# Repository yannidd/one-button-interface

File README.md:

# One Button Interface

PCB layout and schematic and Arduino code for a single push-button interface that can be used to turn a device on/off as well as a user input to interact with the firmware on a microcontroller.

## BOM

Reference   | Quantity| Value                                                                       | RS Stock No.| Vendor
|-          |-        |-                                                                            |-            |-
C1 C2 C3 C5 |4        |1uF                                                                          |461-2708     |RS
C4          |1        |0.1uF                                                                        |264-4630     |RS
H1 H2 H3 H4 |4        |MountingHole                                                                 |~
J1          |1        |[Conn_01x02](https://docs.rs-online.com/cb9d/0900766b81347511.pdf)           |820-1494     |RS
J6          |1        |[Conn_01x04](https://docs.rs-online.com/cd6a/0900766b813c4c2e.pdf)           |360-6314     |RS
R1          |1        |10K                                                                          |182-9211     |RS
SW1         |1        |[PTS645SL50SMTR 92 LFS](https://docs.rs-online.com/62d0/0900766b815a8e9b.pdf)|135-9400     |RS
U1          |1        |[LD39015M33R](http://www.st.com/resource/en/datasheet/ld39015.pdf)           |795-8965     |RS
U2          |1        |[STM6600](http://www.st.com/resource/en/datasheet/stm6600.pdf)               |189-2069     |RS

## Directory Tree

- arduino - Arduino source code with an example application.
- img - Supplementary images
- pcb - PCB schematic, layout and BOM.
  - kicad - Design files for KiCad EDA.

## Connection Diagram

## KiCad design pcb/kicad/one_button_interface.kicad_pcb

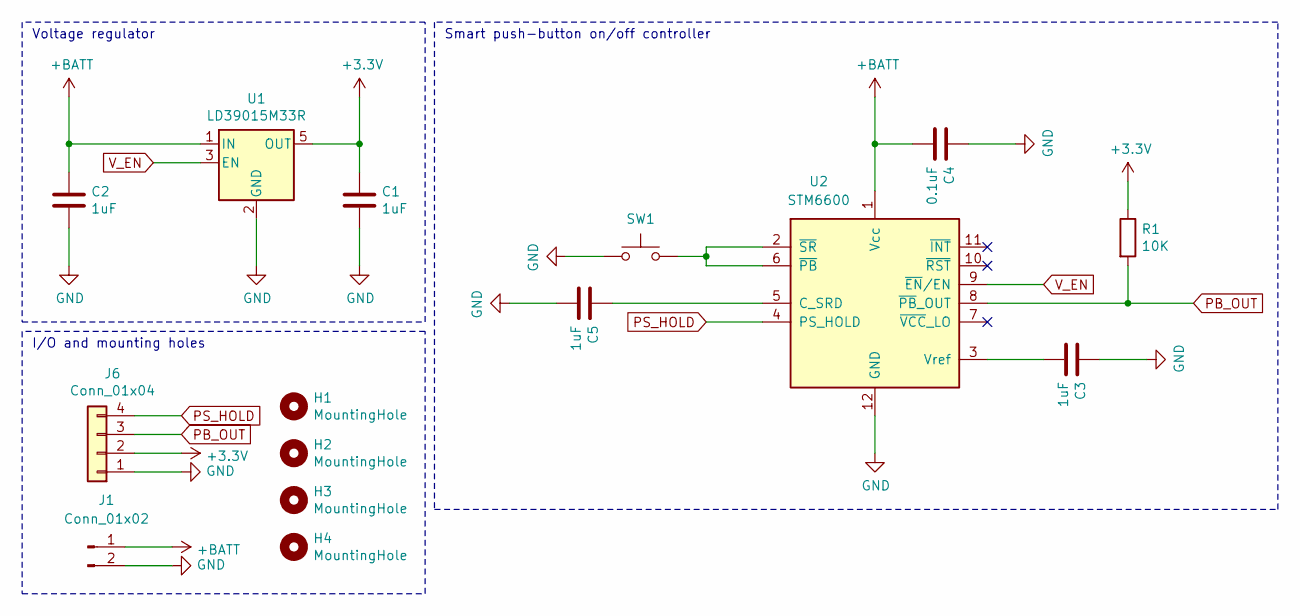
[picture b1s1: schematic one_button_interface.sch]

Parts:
C1, C2, C3, C5: 1uF; C_0603_1608Metric_Pad1.08x0.95mm_HandSolder
C4: 0.1uF; C_0603_1608Metric_Pad1.08x0.95mm_HandSolder
H1, H2, H3, H4: MountingHole; MountingHole_M1.6
J1: Conn_01x02; JST_PH_S2B-PH-K_1x02_P2.00mm_Horizontal
J6: Conn_01x04; PinHeader_1x04_P2.54mm_Vertical
R1: 10K; R_0603_1608Metric_Pad0.98x0.95mm_HandSolder
SW1: PTS645SL50SMTR 92 LFS; SW_SPST_PTS645
U1: LD39015M33R; SOT-23-5
U2: STM6600; TDFN-12_2x3mm_P0.5mm

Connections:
+3V3: C1.1, J6.2, R1.1, U1.5 (OUT)
+BATT: C2.1, C4.2, J1.1, U1.1 (IN), U2.1 (Vcc)
GND: C1.2, C2.2, C3.1, C4.1, C5.2, J1.2, J6.1, SW1.1, U1.2 (GND), U2.12 (GND)
unnamed: C3.2, U2.3 (Vref)
unnamed: C5.1, U2.5 (C_SRD)
unnamed: SW1.2, U2.2 (~SR~), U2.6 (~PB~)
PB_OUT: J6.3, R1.2, U2.8 (~PB~_OUT)
PS_HOLD: J6.4, U2.4 (PS_HOLD)
V_EN: U1.3 (EN), U2.9 (~EN~/EN)

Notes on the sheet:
Voltage regulator
Smart push-button on/off controller
I/O and mounting holes

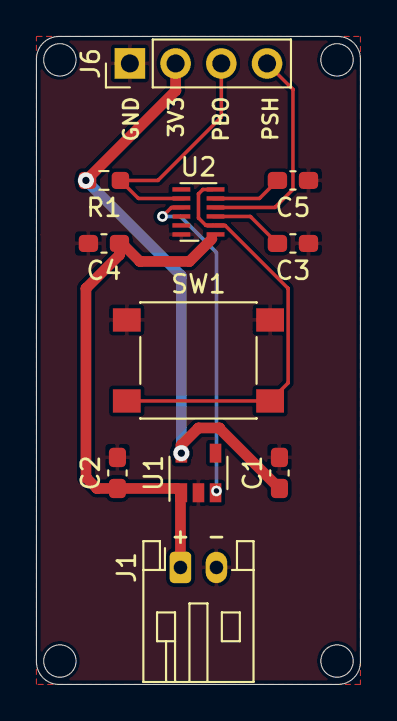
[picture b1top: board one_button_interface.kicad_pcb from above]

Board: 4 copper layers, 18.0 x 36.0 mm, 15 parts (0 on the bottom side), 9 nets.

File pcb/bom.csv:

Reference, Quantity, Value, Footprint, Datasheet, RS Stock No., Vendor
C1 C2 C3 C5 ,4,"1uF","Capacitor_SMD:C_0603_1608Metric_Pad1.08x0.95mm_HandSolder","~","461-2708","RS"
C4 ,1,"0.1uF","Capacitor_SMD:C_0603_1608Metric_Pad1.08x0.95mm_HandSolder","~","264-4630","RS"
H1 H2 H3 H4 ,4,"MountingHole","one_button_interface:MountingHole_M1.6","~"
J1 ,1,"Conn_01x02","Connector_JST:JST_PH_S2B-PH-K_1x02_P2.00mm_Horizontal","https://docs.rs-online.com/cb9d/0900766b81347511.pdf","820-1494","RS"
J6 ,1,"Conn_01x04","Connector_PinHeader_2.54mm:PinHeader_1x04_P2.54mm_Vertical","https://docs.rs-online.com/cd6a/0900766b813c4c2e.pdf","360-6314","RS"
R1 ,1,"10K","Resistor_SMD:R_0603_1608Metric_Pad0.98x0.95mm_HandSolder","~","182-9211","RS"
SW1 ,1,"PTS645SL50SMTR 92 LFS","Button_Switch_SMD:SW_SPST_PTS645","https://docs.rs-online.com/62d0/0900766b815a8e9b.pdf","135-9400","RS"
U1 ,1,"LD39015M33R","Package_TO_SOT_SMD:SOT-23-5","http://www.st.com/resource/en/datasheet/ld39015.pdf","795-8965","RS"
U2 ,1,"STM6600","Package_DFN_QFN:TDFN-12_2x3mm_P0.5mm","http://www.st.com/resource/en/datasheet/stm6600.pdf","189-2069","RS"

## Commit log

2020-11-23 Versioning initial project files.
